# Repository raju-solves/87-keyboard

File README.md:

This project is a custom designed 87% ortholinear mechanical keyboard built as a PCB design and firmware learning experience It includes the PCB layout, CAD files, and firmware and lot of hardwork

I built this project to deepen my understanding of PCB design, keyboard matrix layouts, and CAD designing I wanted hands-on experience creating a mechanical keyboard from the scratch while also designing something practical and customized to my preference

| Name | Description | Quantity | Price (USD) | Link | Vendor |
|------|------------|----------|-------------|------|--------|
| Gateron Mechanical Switches (G Pro 3.0 Yellow Pre-lubed) | Linear pre-lubed keyboard switches (~50g actuation, smooth) | 90 | 17.06 | https://www.thecosmicbyte.com/product/gateron-mechanical-switches-compatible-with-cosmic-byte-hot-swappable-keyboards-qty-1pc/?attribute_pa_switch-type=g-pro-3-0-yellow-pre-lubed | Cosmic Byte |
| Keycaps | Mechanical keyboard keycap set (standard layout) | 90 | 16.19 | https://amzn.in/d/05XbxYkm | Amazon |
| Diodes | General purpose diodes for keyboard matrix | 100 | 2.65 | https://amzn.in/d/0eVDrr6B | Amazon |
| PCB | Custom keyboard printed circuit board | 1 | 42.97 | N/A | JLCPCB |
| RP2040 | Microcontroller board (dual-core ARM Cortex-M0+) | 1 | 8.09 | https://amzn.in/d/00qoAonb | Amazon |
| Screws | Small M2/M2.5 screws for keyboard assembly | 1 pack | 1.53 | https://amzn.in/d/04wa89yN | Amazon |
| Stabilizers | PCB/plate mount stabilizers for larger keys | 1 set | 2.56 | https://www.aliexpress.us/item/3256806342416791.html | AliExpress |
| Soldering Iron | Basic soldering iron for assembling PCB components | 1 | 5.96 | https://amzn.in/d/032QO002 | Amazon |

**Total Cost: 99.01 USD**

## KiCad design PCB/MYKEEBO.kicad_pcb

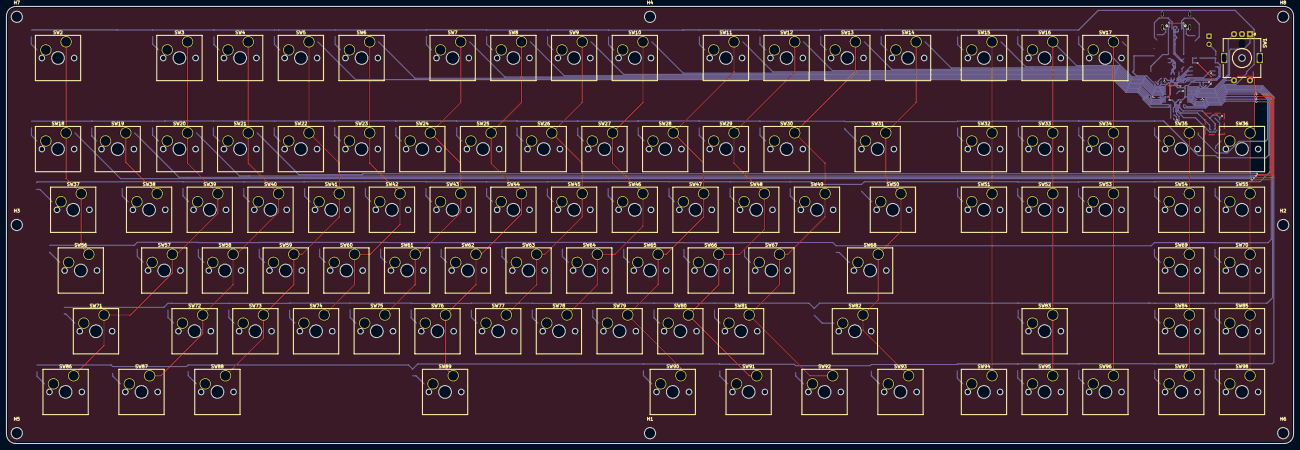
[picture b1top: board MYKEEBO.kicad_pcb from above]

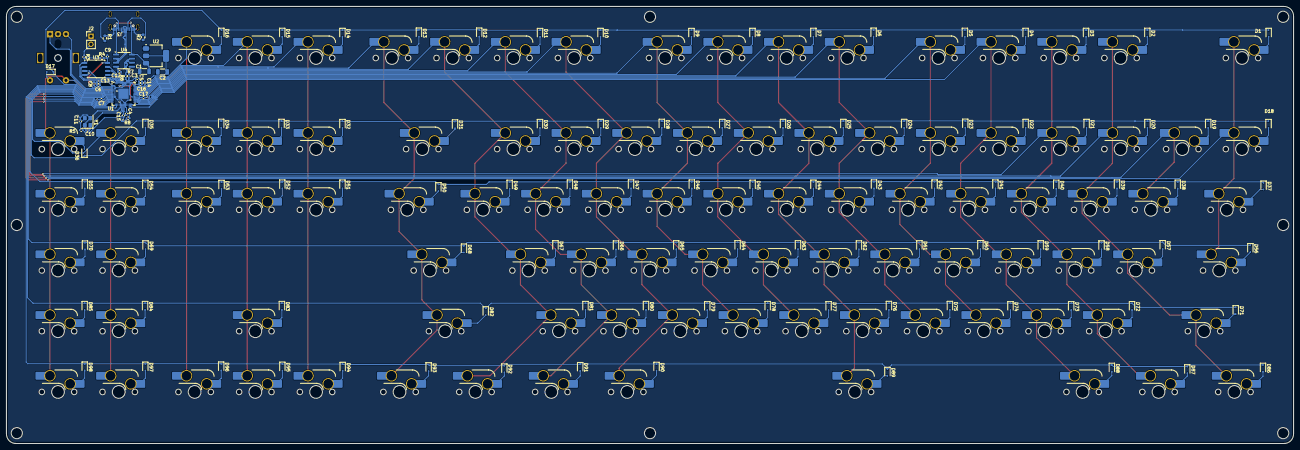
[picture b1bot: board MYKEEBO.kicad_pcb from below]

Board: 2 copper layers, 403.8 x 137.1 mm, 236 parts (130 on the bottom side), 148 nets.

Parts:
C1, C2: C10u; C_1206_3216Metric
C3, C5: C1u; C_0402_1005Metric
C4, C6, C7, C8, C9, C12, C13, C14, C15, C16, C17: C100n; C_0402_1005Metric
C10, C11: C15p; C_0402_1005Metric
D1: Esc; D_SOD-323
D2: F1; D_SOD-323
D3: F2; D_SOD-323
D4: F3; D_SOD-323
D5: F4; D_SOD-323
D6: F5; D_SOD-323
D7: F6; D_SOD-323
D8: F7; D_SOD-323
D9: F8; D_SOD-323
D10: F9; D_SOD-323
D11: F10; D_SOD-323
D12: F11; D_SOD-323
D13: F12; D_SOD-323
D14: PrtScrn; D_SOD-323
D15: Screen Lock; D_SOD-323
D16: Pause; D_SOD-323
D17: D; D_SOD-323
D18: KEY`; D_SOD-323
D19: KEY1; D_SOD-323
D20: KEY2; D_SOD-323
D21: KEY3; D_SOD-323
D22: KEY4; D_SOD-323
D23: KEY5; D_SOD-323
D24: KEY6; D_SOD-323
D25: KEY7; D_SOD-323
D26: KEY8; D_SOD-323
D27: KEY9; D_SOD-323
D28: KEY0; D_SOD-323
D29: KEY-; D_SOD-323
D30: KEY=; D_SOD-323
D31: BKSP; D_SOD-323
D32: Ins; D_SOD-323
D33: Home; D_SOD-323
D34: PgUP; D_SOD-323
D35: M1; D_SOD-323
D36: M2; D_SOD-323
D37: TAB; D_SOD-323
D38: KEYQ; D_SOD-323
D39: KEYW; D_SOD-323
D40: KEYE; D_SOD-323
D41: KEYR; D_SOD-323
D42: KEYT; D_SOD-323
D43: KEYY; D_SOD-323
D44: KEYU; D_SOD-323
D45: KEYI; D_SOD-323
D46: KEYO; D_SOD-323
D47: KEYP; D_SOD-323
D48: KEY[; D_SOD-323
D49: KEY]; D_SOD-323
D50: KEY\; D_SOD-323
D51: Del; D_SOD-323
D52: End; D_SOD-323
D53: PgDN; D_SOD-323
D54: M3; D_SOD-323
D55: M4; D_SOD-323
D56: CAPS; D_SOD-323
D57: KEYA; D_SOD-323
D58: KEYS; D_SOD-323
D59: KEYD; D_SOD-323
D60: KEYF; D_SOD-323
D61: KEYG; D_SOD-323
D62: KEYH; D_SOD-323
D63: KEYJ; D_SOD-323
D64: KEYK; D_SOD-323
D65: KEYL; D_SOD-323
D66: KEY;; D_SOD-323
D67: KEY"; D_SOD-323
D68: ENTER; D_SOD-323
D69: M5; D_SOD-323
D70: M6; D_SOD-323
D71: LSHIFT; D_SOD-323
D72: KEYZ; D_SOD-323
D73: KEYX; D_SOD-323
D74: KEYC; D_SOD-323
D75: KEYV; D_SOD-323
D76: KEYB; D_SOD-323
D77: KEYN; D_SOD-323
D78: KEYM; D_SOD-323
D79: KEY,; D_SOD-323
D80: KEY.; D_SOD-323
D81: KEY/; D_SOD-323
D82: RSHIFT; D_SOD-323
D83: Up Arrow; D_SOD-323
D84: M7; D_SOD-323
D85: M8; D_SOD-323
D86: LCTRL; D_SOD-323
D87: LWIN; D_SOD-323
D88: LALT; D_SOD-323
D89: SPACE; D_SOD-323
D90: RALT; D_SOD-323
D91: RWIN; D_SOD-323
D92: FN; D_SOD-323
D93: RCTRL; D_SOD-323
D94: Left Arrow; D_SOD-323
D95: Down Arrow; D_SOD-323
D96: Right Arrow; D_SOD-323
D97: M9; D_SOD-323
D98: M10; D_SOD-323
H1, H2, H3, H4, H5, H6, H7, H8: MountingHole; MountingHole_3.5mm
J2: Conn_01x02; PinHeader_1x02_P2.54mm_Vertical
J3: USBC; Korean Hroparts Elec - Type C 31 M 12 - 16P - USB 2.0
R1, R2: R5.1k; R_0603_1608Metric
R3: R1K; R_0402_1005Metric
R4: R10K; R_0402_1005Metric
R5: R1k; R_0402_1005Metric
R6, R7: R27.4; R_0402_1005Metric
R8: R10k; R_0402_1005Metric
SW1: RotaryEncoder_Switch; RotaryEncoder_Alps_EC11E-Switch_Vertical_H20mm_MountingHoles
SW2: Esc; SW_Hotswap_Kailh_MX_Plated_1.00u
SW3: F1; SW_Hotswap_Kailh_MX_Plated_1.00u
SW4: F2; SW_Hotswap_Kailh_MX_Plated_1.00u
SW5: F3; SW_Hotswap_Kailh_MX_Plated_1.00u
SW6: F4; SW_Hotswap_Kailh_MX_Plated_1.00u
SW7: F5; SW_Hotswap_Kailh_MX_Plated_1.00u
SW8: F6; SW_Hotswap_Kailh_MX_Plated_1.00u
SW9: F7; SW_Hotswap_Kailh_MX_Plated_1.00u
SW10: F8; SW_Hotswap_Kailh_MX_Plated_1.00u
SW11: F9; SW_Hotswap_Kailh_MX_Plated_1.00u
SW12: F10; SW_Hotswap_Kailh_MX_Plated_1.00u
SW13: F11; SW_Hotswap_Kailh_MX_Plated_1.00u
SW14: F12; SW_Hotswap_Kailh_MX_Plated_1.00u
SW15: PrtScrn; SW_Hotswap_Kailh_MX_Plated_1.00u
SW16: Screen Lock; SW_Hotswap_Kailh_MX_Plated_1.00u
SW17: Pause; SW_Hotswap_Kailh_MX_Plated_1.00u
SW18: KEY`; SW_Hotswap_Kailh_MX_Plated_1.00u
SW19: KEY1; SW_Hotswap_Kailh_MX_Plated_1.00u
SW20: KEY2; SW_Hotswap_Kailh_MX_Plated_1.00u
SW21: KEY3; SW_Hotswap_Kailh_MX_Plated_1.00u
SW22: KEY4; SW_Hotswap_Kailh_MX_Plated_1.00u
SW23: KEY5; SW_Hotswap_Kailh_MX_Plated_1.00u
SW24: KEY6; SW_Hotswap_Kailh_MX_Plated_1.00u
SW25: KEY7; SW_Hotswap_Kailh_MX_Plated_1.00u
SW26: KEY8; SW_Hotswap_Kailh_MX_Plated_1.00u
SW27: KEY9; SW_Hotswap_Kailh_MX_Plated_1.00u
SW28: KEY0; SW_Hotswap_Kailh_MX_Plated_1.00u
SW29: KEY-; SW_Hotswap_Kailh_MX_Plated_1.00u
SW30: KEY=; SW_Hotswap_Kailh_MX_Plated_1.00u
SW31: BKSP; SW_Hotswap_Kailh_MX_Plated_2.00u
SW32: Ins; SW_Hotswap_Kailh_MX_Plated_1.00u
SW33: Home; SW_Hotswap_Kailh_MX_Plated_1.00u
SW34: PgUP; SW_Hotswap_Kailh_MX_Plated_1.00u
SW35: M1; SW_Hotswap_Kailh_MX_Plated_1.00u
SW36: M2; SW_Hotswap_Kailh_MX_Plated_1.00u
SW37: TAB; SW_Hotswap_Kailh_MX_Plated_1.50u
SW38: KEYQ; SW_Hotswap_Kailh_MX_Plated_1.00u
SW39: KEYW; SW_Hotswap_Kailh_MX_Plated_1.00u
SW40: KEYE; SW_Hotswap_Kailh_MX_Plated_1.00u
SW41: KEYR; SW_Hotswap_Kailh_MX_Plated_1.00u
SW42: KEYT; SW_Hotswap_Kailh_MX_Plated_1.00u
SW43: KEYY; SW_Hotswap_Kailh_MX_Plated_1.00u
SW44: KEYU; SW_Hotswap_Kailh_MX_Plated_1.00u
SW45: KEYI; SW_Hotswap_Kailh_MX_Plated_1.00u
SW46: KEYO; SW_Hotswap_Kailh_MX_Plated_1.00u
SW47: KEYP; SW_Hotswap_Kailh_MX_Plated_1.00u
SW48: KEY[; SW_Hotswap_Kailh_MX_Plated_1.00u
SW49: KEY]; SW_Hotswap_Kailh_MX_Plated_1.00u
SW50: KEY\; SW_Hotswap_Kailh_MX_Plated_1.50u
SW51: Del; SW_Hotswap_Kailh_MX_Plated_1.00u
SW52: End; SW_Hotswap_Kailh_MX_Plated_1.00u
SW53: PgDN; SW_Hotswap_Kailh_MX_Plated_1.00u
SW54: M3; SW_Hotswap_Kailh_MX_Plated_1.00u
SW55: M4; SW_Hotswap_Kailh_MX_Plated_1.00u
SW56: CAPS; SW_Hotswap_Kailh_MX_Plated_1.75u
SW57: KEYA; SW_Hotswap_Kailh_MX_Plated_1.00u
SW58: KEYS; SW_Hotswap_Kailh_MX_Plated_1.00u
SW59: KEYD; SW_Hotswap_Kailh_MX_Plated_1.00u
SW60: KEYF; SW_Hotswap_Kailh_MX_Plated_1.00u
SW61: KEYG; SW_Hotswap_Kailh_MX_Plated_1.00u
SW62: KEYH; SW_Hotswap_Kailh_MX_Plated_1.00u
SW63: KEYJ; SW_Hotswap_Kailh_MX_Plated_1.00u
SW64: KEYK; SW_Hotswap_Kailh_MX_Plated_1.00u
SW65: KEYL; SW_Hotswap_Kailh_MX_Plated_1.00u
SW66: KEY;; SW_Hotswap_Kailh_MX_Plated_1.00u
SW67: KEY"; SW_Hotswap_Kailh_MX_Plated_1.00u
SW68: ENTER; SW_Hotswap_Kailh_MX_Plated_2.25u
SW69: M5; SW_Hotswap_Kailh_MX_Plated_1.00u
SW70: M6; SW_Hotswap_Kailh_MX_Plated_1.00u
SW71: LSHIFT; SW_Hotswap_Kailh_MX_Plated_2.25u
SW72: KEYZ; SW_Hotswap_Kailh_MX_Plated_1.00u
SW73: KEYX; SW_Hotswap_Kailh_MX_Plated_1.00u
SW74: KEYC; SW_Hotswap_Kailh_MX_Plated_1.00u
SW75: KEYV; SW_Hotswap_Kailh_MX_Plated_1.00u
SW76: KEYB; SW_Hotswap_Kailh_MX_Plated_1.00u
SW77: KEYN; SW_Hotswap_Kailh_MX_Plated_1.00u
SW78: KEYM; SW_Hotswap_Kailh_MX_Plated_1.00u
SW79: KEY,; SW_Hotswap_Kailh_MX_Plated_1.00u
SW80: KEY.; SW_Hotswap_Kailh_MX_Plated_1.00u
SW81: KEY/; SW_Hotswap_Kailh_MX_Plated_1.00u
SW82: RSHIFT; SW_Hotswap_Kailh_MX_Plated_2.75u
SW83: Up Arrow; SW_Hotswap_Kailh_MX_Plated_1.00u
SW84: M7; SW_Hotswap_Kailh_MX_Plated_1.00u
SW85: M8; SW_Hotswap_Kailh_MX_Plated_1.00u
SW86: LCTRL; SW_Hotswap_Kailh_MX_Plated_1.25u
SW87: LWIN; SW_Hotswap_Kailh_MX_Plated_1.25u
SW88: LALT; SW_Hotswap_Kailh_MX_Plated_1.25u
SW89: SPACE; SW_Hotswap_Kailh_MX_Plated_6.25u
SW90: RALT; SW_Hotswap_Kailh_MX_Plated_1.25u
SW91: RWIN; SW_Hotswap_Kailh_MX_Plated_1.25u
SW92: FN; SW_Hotswap_Kailh_MX_Plated_1.25u
SW93: RCTRL; SW_Hotswap_Kailh_MX_Plated_1.25u
SW94: Left Arrow; SW_Hotswap_Kailh_MX_Plated_1.00u
SW95: Down Arrow; SW_Hotswap_Kailh_MX_Plated_1.00u
SW96: Right Arrow; SW_Hotswap_Kailh_MX_Plated_1.00u
SW97: M9; SW_Hotswap_Kailh_MX_Plated_1.00u
SW98: M10; SW_Hotswap_Kailh_MX_Plated_1.00u
U1: RP2040; QFN-56-1EP_7x7mm_P0.4mm_EP3.2x3.2mm
U2: NCP1117-3.3_SOT223; SOT-223-3_TabPin2
U3: W25Q128JVS; SOIC-8_5.3x5.3mm_P1.27mm
U4: USB6B1; SOIC-8_3.9x4.9mm_P1.27mm
Y1: Crystal_GND24; Crystal_SMD_3225-4Pin_3.2x2.5mm

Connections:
+1V1: C3.2, C4.1, C12.1, U1.23 (DVDD), U1.45 (VREG_VOUT), U1.50 (DVDD)
+3.3V: C2.1, C5.1, C6.1, C7.1, C8.1, C9.1, C13.1, C14.1, C15.1, C16.1, C17.1, R4.2, R8.1, U1.1 (IOVDD), U1.10 (IOVDD), U1.22 (IOVDD), U1.33 (IOVDD), U1.42 (IOVDD), U1.43 (ADC_AVDD), U1.44 (VREG_IN), U1.48 (USB_VDD), U1.49 (IOVDD), U2.2 (VO), U3.8 (VCC)
+5V: C1.1, J3.A4/B9 (VBUS), J3.B4/A9 (VBUS), U2.3 (VI), U4.1 (VBUS), U4.8 (VBUS)
/D+: R6.1, U4.7 (I/O1)
/D-: R7.1, U4.6 (I/O2)
/PI_D+: R6.2, U1.47 (USB_DP)
/PI_D-: R7.2, U1.46 (USB_DM)
/QSPI_SCLK: U1.52 (QSPI_SCLK), U3.6 (CLK)
/QSPI_SD0: U1.53 (QSPI_SD0), U3.5 (DI/IO_{0})
/QSPI_SD1: U1.55 (QSPI_SD1), U3.2 (DO/IO_{1})
/QSPI_SD2: U1.54 (QSPI_SD2), U3.3 (~WP/IO_{2})
/QSPI_SD3: U1.51 (QSPI_SD3), U3.7 (~HOLD/~RESET/IO_{3})
/QSPI_SS: R3.2, R4.1, U1.56 (QSPI_SS), U3.1 (~CS)
/USB_D+: J3.A6 (DP1), J3.B6 (DP2), U4.2 (I/O1)
/USB_D-: J3.A7 (DN1), J3.B7 (DN2), U4.3 (I/O2)
/XIN: C10.2, U1.20 (XIN), Y1.1
/XOUT: R5.1, U1.21 (XOUT)
COL1: SW2.2, SW18.2, SW37.2, SW56.2, U1.13 (GPIO10)
COL2: SW19.2, SW38.2, U1.14 (GPIO11)
COL3: SW3.2, SW20.2, SW39.2, SW57.2, SW71.2, SW86.2, U1.15 (GPIO12)
COL4: SW4.2, SW21.2, SW40.2, SW58.2, SW72.2, SW87.2, U1.16 (GPIO13)
COL5: SW5.2, SW22.2, SW41.2, SW59.2, SW73.2, SW88.2, U1.27 (GPIO16)
COL6: SW6.2, SW23.2, SW42.2, SW60.2, SW74.2, U1.28 (GPIO17)
COL7: SW7.2, SW24.2, SW43.2, SW61.2, SW75.2, U1.29 (GPIO18)
COL8: SW8.2, SW25.2, SW44.2, SW62.2, SW76.2, SW89.2, U1.30 (GPIO19)
COL9: SW9.2, SW26.2, SW45.2, SW63.2, SW77.2, U1.31 (GPIO20)
COL10: SW10.2, SW27.2, SW46.2, SW64.2, SW78.2, U1.32 (GPIO21)
COL11: SW11.2, SW28.2, SW47.2, SW65.2, SW79.2, SW90.2, U1.35 (GPIO23)
COL12: SW12.2, SW29.2, SW48.2, SW66.2, SW80.2, SW91.2, U1.36 (GPIO24)
COL13: SW13.2, SW30.2, SW49.2, SW67.2, SW81.2, SW92.2, U1.37 (GPIO25)
COL14: SW14.2, SW31.2, SW50.2, SW68.2, SW82.2, SW93.2, U1.38 (GPIO26_ADC0)
COL15: SW15.2, SW32.2, SW51.2, SW94.2, U1.39 (GPIO27_ADC1)
COL16: SW16.2, SW33.2, SW52.2, SW83.2, SW95.2, U1.40 (GPIO28_ADC2)
COL17: SW17.2, SW34.2, SW53.2, SW96.2, U1.41 (GPIO29_ADC3)
COL18: SW35.2, SW54.2, SW69.2, SW84.2, SW97.2, U1.12 (GPIO9)
COL19: SW1.S1, SW36.2, SW55.2, SW70.2, SW85.2, SW98.2, U1.4 (GPIO2)
GND: C1.2, C2.2, C3.1, C4.2, C5.2, C6.2, C7.2, C8.2, C9.2, C10.1, C11.2, C12.2, C13.2, C14.2, C15.2, C16.2, C17.2, J2.1, J3.A1/B12 (GND), J3.B1/A12 (GND), J3.SH, R1.2, R2.2, SW1.C, U1.19 (TESTEN), U1.57 (GND), U2.1 (GND), U3.4 (GND), U4.4 (GND), U4.5 (GND), Y1.2, Y1.4
unnamed: C11.1, R5.2, Y1.3
unnamed: D1.2 (A), SW2.1
unnamed: D2.2 (A), SW3.1
unnamed: D3.2 (A), SW4.1
unnamed: D4.2 (A), SW5.1
unnamed: D5.2 (A), SW6.1
unnamed: D6.2 (A), SW7.1
unnamed: D7.2 (A), SW8.1
unnamed: D8.2 (A), SW9.1
unnamed: D9.2 (A), SW10.1
unnamed: D10.2 (A), SW11.1
unnamed: D11.2 (A), SW12.1
unnamed: D12.2 (A), SW13.1
unnamed: D13.2 (A), SW14.1
unnamed: D14.2 (A), SW15.1
unnamed: D15.2 (A), SW16.1
unnamed: D16.2 (A), SW17.1
unnamed: D17.2 (A), SW1.S2
unnamed: D18.2 (A), SW18.1
unnamed: D19.2 (A), SW19.1
unnamed: D20.2 (A), SW20.1
unnamed: D21.2 (A), SW21.1
unnamed: D22.2 (A), SW22.1
unnamed: D23.2 (A), SW23.1
unnamed: D24.2 (A), SW24.1
unnamed: D25.2 (A), SW25.1
unnamed: D26.2 (A), SW26.1
unnamed: D27.2 (A), SW27.1
unnamed: D28.2 (A), SW28.1
unnamed: D29.2 (A), SW29.1
unnamed: D30.2 (A), SW30.1
unnamed: D31.2 (A), SW31.1
unnamed: D32.2 (A), SW32.1
unnamed: D33.2 (A), SW33.1
unnamed: D34.2 (A), SW34.1
unnamed: D35.2 (A), SW35.1
unnamed: D36.2 (A), SW36.1
unnamed: D37.2 (A), SW37.1
unnamed: D38.2 (A), SW38.1
unnamed: D39.2 (A), SW39.1
unnamed: D40.2 (A), SW40.1
unnamed: D41.2 (A), SW41.1
unnamed: D42.2 (A), SW42.1
unnamed: D43.2 (A), SW43.1
unnamed: D44.2 (A), SW44.1
unnamed: D45.2 (A), SW45.1
unnamed: D46.2 (A), SW46.1
unnamed: D47.2 (A), SW47.1
unnamed: D48.2 (A), SW48.1
unnamed: D49.2 (A), SW49.1
unnamed: D50.2 (A), SW50.1
unnamed: D51.2 (A), SW51.1
unnamed: D52.2 (A), SW52.1
unnamed: D53.2 (A), SW53.1
unnamed: D54.2 (A), SW54.1
unnamed: D55.2 (A), SW55.1
unnamed: D56.2 (A), SW56.1
unnamed: D57.2 (A), SW57.1
unnamed: D58.2 (A), SW58.1
unnamed: D59.2 (A), SW59.1
unnamed: D60.2 (A), SW60.1
unnamed: D61.2 (A), SW61.1
unnamed: D62.2 (A), SW62.1
unnamed: D63.2 (A), SW63.1
unnamed: D64.2 (A), SW64.1
unnamed: D65.2 (A), SW65.1
unnamed: D66.2 (A), SW66.1
unnamed: D67.2 (A), SW67.1
unnamed: D68.2 (A), SW68.1
unnamed: D69.2 (A), SW69.1
unnamed: D70.2 (A), SW70.1
unnamed: D71.2 (A), SW71.1
unnamed: D72.2 (A), SW72.1
unnamed: D73.2 (A), SW73.1
unnamed: D74.2 (A), SW74.1
unnamed: D75.2 (A), SW75.1
unnamed: D76.2 (A), SW76.1
unnamed: D77.2 (A), SW77.1
unnamed: D78.2 (A), SW78.1
unnamed: D79.2 (A), SW79.1
unnamed: D80.2 (A), SW80.1
unnamed: D81.2 (A), SW81.1
unnamed: D82.2 (A), SW82.1
unnamed: D83.2 (A), SW83.1
unnamed: D84.2 (A), SW84.1
unnamed: D85.2 (A), SW85.1
unnamed: D86.2 (A), SW86.1
unnamed: D87.2 (A), SW87.1
unnamed: D88.2 (A), SW88.1
unnamed: D89.2 (A), SW89.1
unnamed: D90.2 (A), SW90.1
unnamed: D91.2 (A), SW91.1
unnamed: D92.2 (A), SW92.1
unnamed: D93.2 (A), SW93.1
unnamed: D94.2 (A), SW94.1
unnamed: D95.2 (A), SW95.1
unnamed: D96.2 (A), SW96.1
unnamed: D97.2 (A), SW97.1
unnamed: D98.2 (A), SW98.1
unnamed: J2.2, R3.1
unnamed: J3.A5 (CC1), R2.1
unnamed: J3.B5 (CC2), R1.1
unnamed: R8.2, U1.26 (RUN)
ROTA: SW1.A, U1.3 (GPIO1)
ROTB: SW1.B, U1.2 (GPIO0)
ROW1: D1.1 (K), D2.1 (K), D3.1 (K), D4.1 (K), D5.1 (K), D6.1 (K), D7.1 (K), D8.1 (K), D9.1 (K), D10.1 (K), D11.1 (K), D12.1 (K), D13.1 (K), D14.1 (K), D15.1 (K), D16.1 (K), D17.1 (K), U1.5 (GPIO3)
ROW2: D18.1 (K), D19.1 (K), D20.1 (K), D21.1 (K), D22.1 (K), D23.1 (K), D24.1 (K), D25.1 (K), D26.1 (K), D27.1 (K), D28.1 (K), D29.1 (K), D30.1 (K), D31.1 (K), D32.1 (K), D33.1 (K), D34.1 (K), D35.1 (K), D36.1 (K), U1.11 (GPIO8)
ROW3: D37.1 (K), D38.1 (K), D39.1 (K), D40.1 (K), D41.1 (K), D42.1 (K), D43.1 (K), D44.1 (K), D45.1 (K), D46.1 (K), D47.1 (K), D48.1 (K), D49.1 (K), D50.1 (K), D51.1 (K), D52.1 (K), D53.1 (K), D54.1 (K), D55.1 (K), U1.9 (GPIO7)
ROW4: D56.1 (K), D57.1 (K), D58.1 (K), D59.1 (K), D60.1 (K), D61.1 (K), D62.1 (K), D63.1 (K), D64.1 (K), D65.1 (K), D66.1 (K), D67.1 (K), D68.1 (K), D69.1 (K), D70.1 (K), U1.8 (GPIO6)
ROW5: D71.1 (K), D72.1 (K), D73.1 (K), D74.1 (K), D75.1 (K), D76.1 (K), D77.1 (K), D78.1 (K), D79.1 (K), D80.1 (K), D81.1 (K), D82.1 (K), D83.1 (K), D84.1 (K), D85.1 (K), U1.7 (GPIO5)
ROW6: D86.1 (K), D87.1 (K), D88.1 (K), D89.1 (K), D90.1 (K), D91.1 (K), D92.1 (K), D93.1 (K), D94.1 (K), D95.1 (K), D96.1 (K), D97.1 (K), D98.1 (K), U1.6 (GPIO4)
